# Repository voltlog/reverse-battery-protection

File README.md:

# Reverse Battery Protection Using N-ch Mosfet
I designed this circuit to show a simple circuit to achieve reverse battery protection in low power devices. Everyone knows the classic solution of using an in-line diode but that has one major drawback: the voltage drop on the diode. If your circuit is powered by a CR2032 you can’t afford losing 0.5V on the diode. The circuit I’m showing uses a mosfet to achieve the protection feature but minimises the voltage drop and the losses because a mosfet will have a very low internal resistance when conducting.

More info about this project in [Voltlog #353](https://youtu.be/ag2LE_MbWCE).

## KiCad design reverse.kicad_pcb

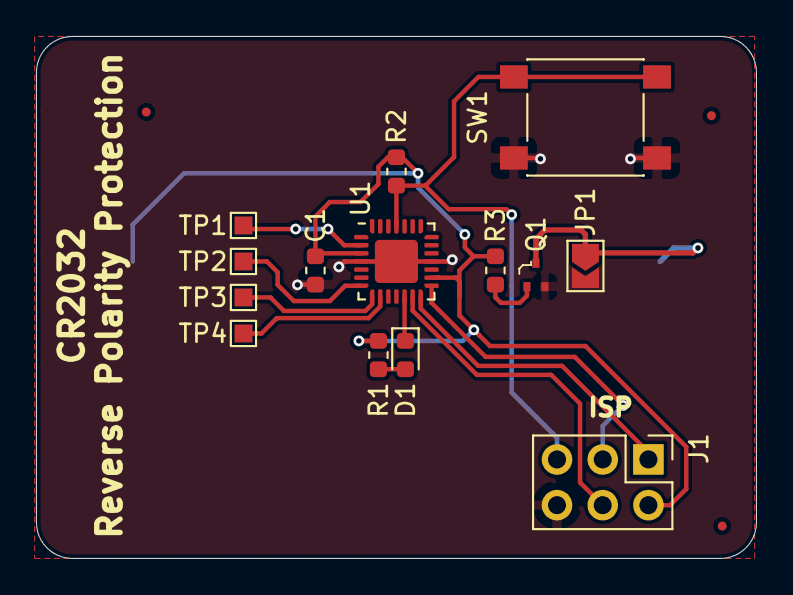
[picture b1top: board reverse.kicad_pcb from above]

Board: 2 copper layers, 40.0 x 29.0 mm, 19 parts (1 on the bottom side), 14 nets.

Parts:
BT1: Battery_Cell; BatteryHolder_Keystone_1060_1x2032
C1: 0.1uF; C_0603_1608Metric
D1: LED_ALT; LED_0603_1608Metric
FID1, FID2, FID3: Fiducial; Fiducial_0.5mm_Mask1mm
J1: AVR-ISP-6; PinHeader_2x03_P2.54mm_Vertical
JP1: Jumper_2_Open; SolderJumper-2_P1.3mm_Open_TrianglePad1.0x1.5mm
Q1: DMG1012T-7; sot-523
R1: 120R; R_0603_1608Metric
R2: 100K; R_0603_1608Metric
R3: 1K; R_0603_1608Metric
SW1: SW_Push; SW_Push_1P1T_NO_6x6mm_H9.5mm
TP1, TP2, TP3, TP4: TestPoint; TestPoint_Pad_1.0x1.0mm
U1: ATtiny48-MMU; QFN-28-1EP_4x4mm_P0.45mm_EP2.4x2.4mm
V1: VOLTLOG_LOGO; voltlog_mask_3mm

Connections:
+BATT: BT1.1, C1.1, J1.2, R1.1, R2.1, R3.1, U1.3, U1.16
/PB3: J1.4, U1.13
/PB4: J1.1, U1.14
/PB5: J1.3, U1.15
/RESET: J1.5, R2.2, SW1.1, U1.25
GND: C1.2, J1.6, JP1.2, Q1.2, SW1.2, U1.4, U1.18, U1.29
unnamed: BT1.2, JP1.1, Q1.3
unnamed: D1.1, U1.12
unnamed: D1.2, R1.2
unnamed: Q1.1, R3.2
unnamed: TP1.1, U1.2
unnamed: TP2.1, U1.7
unnamed: TP3.1, U1.8
unnamed: TP4.1, U1.9

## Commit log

2021-03-03 Fixed a problem with mosfet having drain and source reversed.
